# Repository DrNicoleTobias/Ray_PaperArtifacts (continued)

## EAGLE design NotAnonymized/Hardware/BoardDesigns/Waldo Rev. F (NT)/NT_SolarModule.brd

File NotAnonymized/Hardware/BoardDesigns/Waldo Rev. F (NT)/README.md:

#Waldo Rev. F (NT)
Status:  Currently being developed/tested - Under construction.

This folder contains all of the board and schematic files associated with the three Waldo modules (Solar Processing, MCU, and Radio Modules).  Gerbers generated from these files are zipped by module and also included in the Gerbers folder.  References to modified notes associated with Rev D are located in the References folder for the meantime.  A complete BOM as of this date is included and separated by module along with a combined list for ordering for all three modules at once.   The makefile that is included only provides a clean tag to help clean up any of the junk files from this folder as users edit the .brd and .sch files, if they choose to use it.

Current operating version (This is the version used in the ITW deployment for TOSN submission):  
(WALDO v2) Solar2 > MCU1 < Radio

-->Note:  Documentation of this Waldo hardware revision has been developed by Nicole Tobias, Oct 2018.  Let me know if you have additional questions or concerns.

Major updates from Rev. D PCB:
(- removed, + added, +/- modified)
v0
	+/- MCU has been upgraded to a MSP430FR5994 microcontroller.
	+/- Modified how the modules interconnect and modified shape to be smaller and more linear for ease of developing a case to if needed for this PCB..
	+ Added the ability to be able to capture raw wave forms and added active probe circuitry to accomplish reading these signals without effecting them by reading them.
	+/- Changed many of the exposed headers to be probe pads instead to reduce space when not needed, and to help uncomplicate soldering tasks later.
	+/- Changed all possible resistors and capacitors to 0603, instead of 0805 to help reduce space as well.
	- Removed Real-Time Clock, Digipots, etc circuitry to clean up design since they were not being populated in Rev. D.
	+/- Combined both solar boards into one board.
	+ Switch added to solar board to assist with discharging capacitors when needed.
	+/- Switches on MCU module for external battery power, replaced with a jumper to reduce space and confusion on board.
v1
	+ added a 47k resistor and 2.2nF capacitor on the reset pin as specified on the datasheet
	+ added version number to brd silkscreen
	+/- removed +3V3 parts from schematic and changed to DVCC labels for readability and to lower confusion.
v2
	+/- changed resistor and capacitor values on the filters and resistor dividers to decrease power loss over those parts of the circuit.
	+ added connections on the solar board to allow for raw signal reading by the MCU module.
	+/- Moved low pass filters out of the path of the harvesting circuit on the solar board.

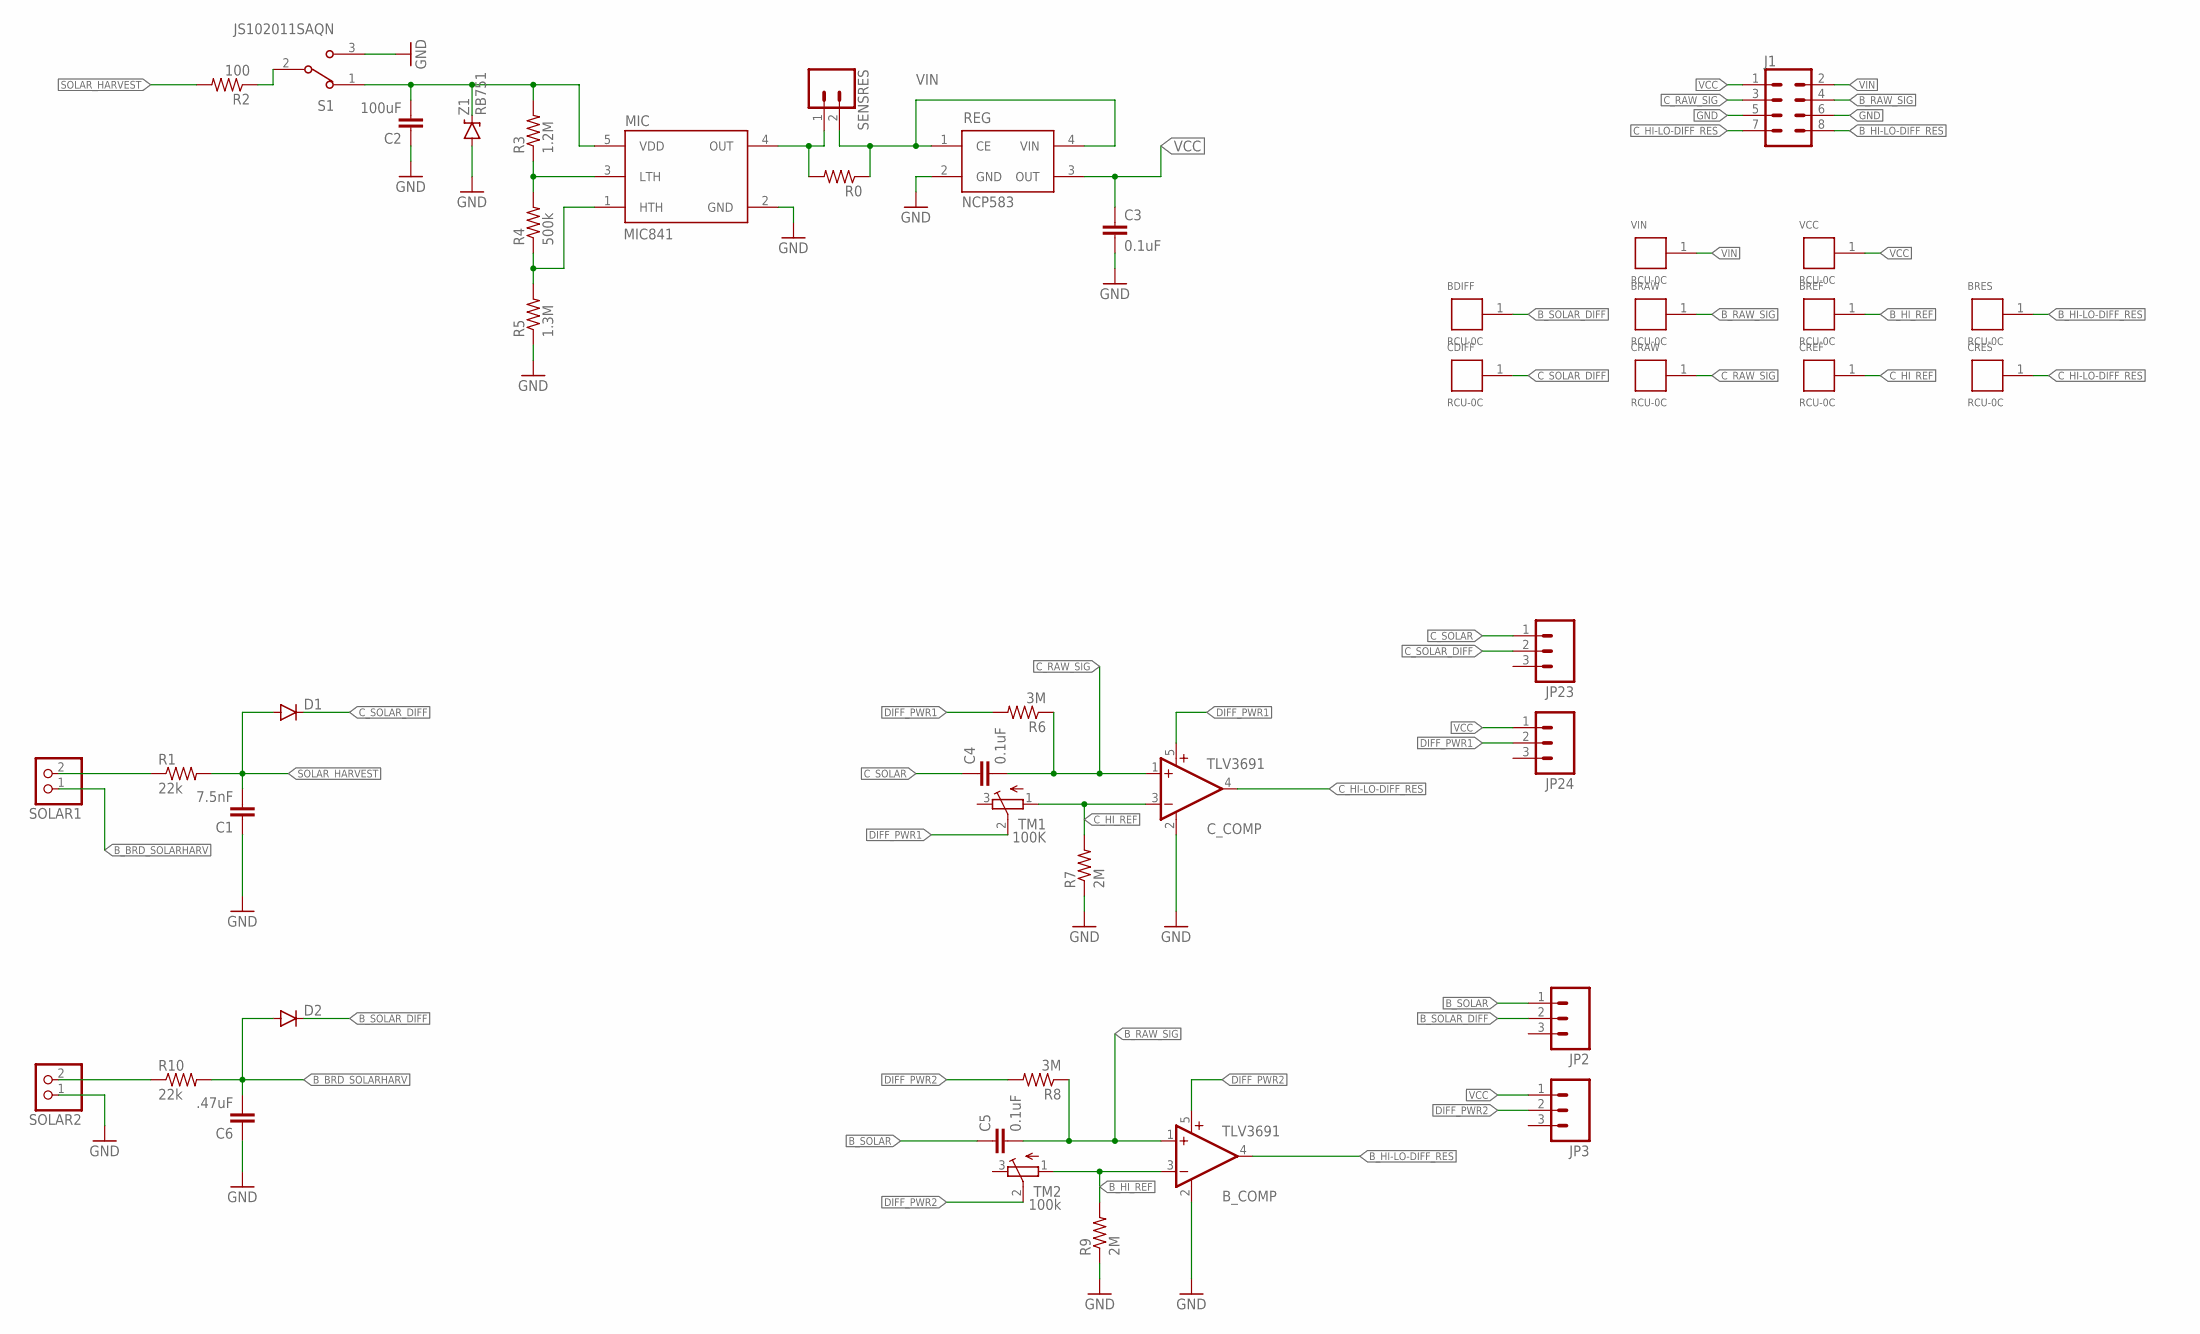
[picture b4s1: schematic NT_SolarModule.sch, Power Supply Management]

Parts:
BDIFF: RCU-0C; TE_RCU-0C
BRAW: RCU-0C; TE_RCU-0C
BREF: RCU-0C; TE_RCU-0C
BRES: RCU-0C; TE_RCU-0C
B_COMP: TLV3691; SC70-5
C1: 7.5nF; 0603-CAP
C2: 100uF; 0603-CAP
C3, C4, C5: 0.1uF; 0603-CAP
C6: .47uF; 0603-CAP
CDIFF: RCU-0C; TE_RCU-0C
CRAW: RCU-0C; TE_RCU-0C
CREF: RCU-0C; TE_RCU-0C
CRES: RCU-0C; TE_RCU-0C
C_COMP: TLV3691; SC70-5
D1, D2: DIODESOD523; SOD523
J1: CONN_04X2; 2X4
JP2, JP3, JP23, JP24: M03; 1X03-1.27MM
MIC: MIC841; SC70-5
R0: RESISTOR0603; 0603-RES
R1, R10: 22k; 0603-RES
R2: 100; 0603-RES
R3: 1.2M; 0603-RES
R4: 500k; 0603-RES
R5: 1.3M; 0603-RES
R6, R8: 3M; 0603-RES
R7, R9: 2M; 0603-RES
REG: NCP583; SC82-AB_1PRIMARY
S1: JS102011SAQN; SW_JS102011SAQN
SENSRES: CONN_02; 1X02
SOLAR1, SOLAR2: PINHD-1X2; 1X02
TM1: 100K; TC33X
TM2: 100k; TC33X
VCC: RCU-0C; TE_RCU-0C
VIN: RCU-0C; TE_RCU-0C
Z1: RB751; SOD-523

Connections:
B_BRD_SOLARHARV: C6.2, D2.A, R10.2, SOLAR1.1
B_HI-LO-DIFF_RES: BRES.1, B_COMP.4 (OUT), J1.8
B_HI_REF: BREF.1, B_COMP.3 (-IN), R9.2, TM2.1 (A)
B_RAW_SIG: BRAW.1, B_COMP.1 (+IN), C5.2, J1.4, R8.1
B_SOLAR: C5.1, JP2.1
B_SOLAR_DIFF: BDIFF.1, D2.C, JP2.2
C_HI-LO-DIFF_RES: CRES.1, C_COMP.4 (OUT), J1.7
C_HI_REF: CREF.1, C_COMP.3 (-IN), R7.2, TM1.1 (A)
C_RAW_SIG: C4.2, CRAW.1, C_COMP.1 (+IN), J1.3, R6.1
C_SOLAR: C4.1, JP23.1
C_SOLAR_DIFF: CDIFF.1, D1.C, JP23.2
DIFF_PWR1: C_COMP.5 (V+), JP24.2, R6.2, TM1.2 (S)
DIFF_PWR2: B_COMP.5 (V+), JP3.2, R8.2, TM2.2 (S)
GND: B_COMP.2 (GND), C1.1, C2.1, C3.2, C6.1, C_COMP.2 (GND), J1.5, J1.6, MIC.2 (GND), R5.1, R7.1, R9.1, REG.2 (GND), S1.3, SOLAR2.1, Z1.ANODE (A)
MIC_INPUT: C2.2, MIC.5 (VDD), R3.2, S1.1, Z1.CATHODE (C)
unnamed: MIC.4 (OUT), R0.2, SENSRES.1
unnamed: R2.1, S1.2
unnamed: MIC.3 (LTH), R3.1, R4.2
unnamed: MIC.1 (HTH), R4.1, R5.2
SOLAR1: R1.1, SOLAR1.2
SOLAR2: R10.1, SOLAR2.2
SOLAR_HARVEST: C1.2, D1.A, R1.2, R2.2
VCC: C3.1, J1.1, JP3.1, JP24.1, REG.3 (OUT), VCC.1
VIN: J1.2, R0.1, REG.1 (CE), REG.4 (VIN), SENSRES.2, VIN.1

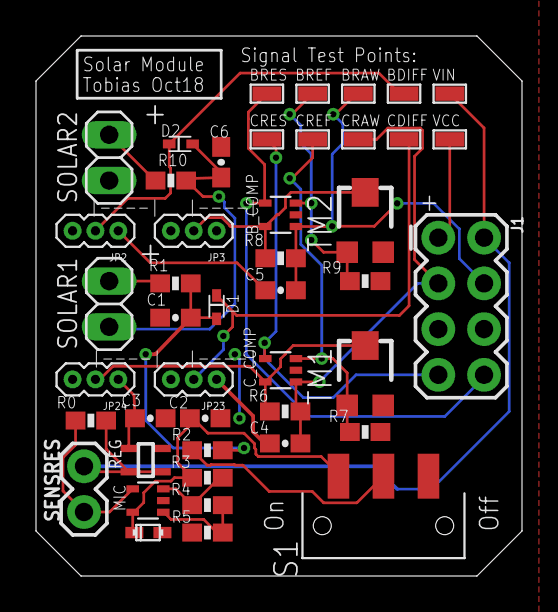
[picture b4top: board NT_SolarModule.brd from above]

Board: 2 copper layers, 27.0 x 30.0 mm, 45 parts (0 on the bottom side), 24 nets.

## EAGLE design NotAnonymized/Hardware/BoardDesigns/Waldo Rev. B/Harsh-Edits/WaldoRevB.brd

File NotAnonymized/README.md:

# RAY

**RAY** is a project whose goal is to accomplish batteryless occupancy detection.  

This repo stores code, hardware files, and other technical documents for the project. Subdirectories are described below.

### Software
Source code, testing code, and documentation.

### Hardware
Hardware PCB version files, 3D enclosures, and documentation.

### Papers
All files, data, and figures used in submission attempts for this project.

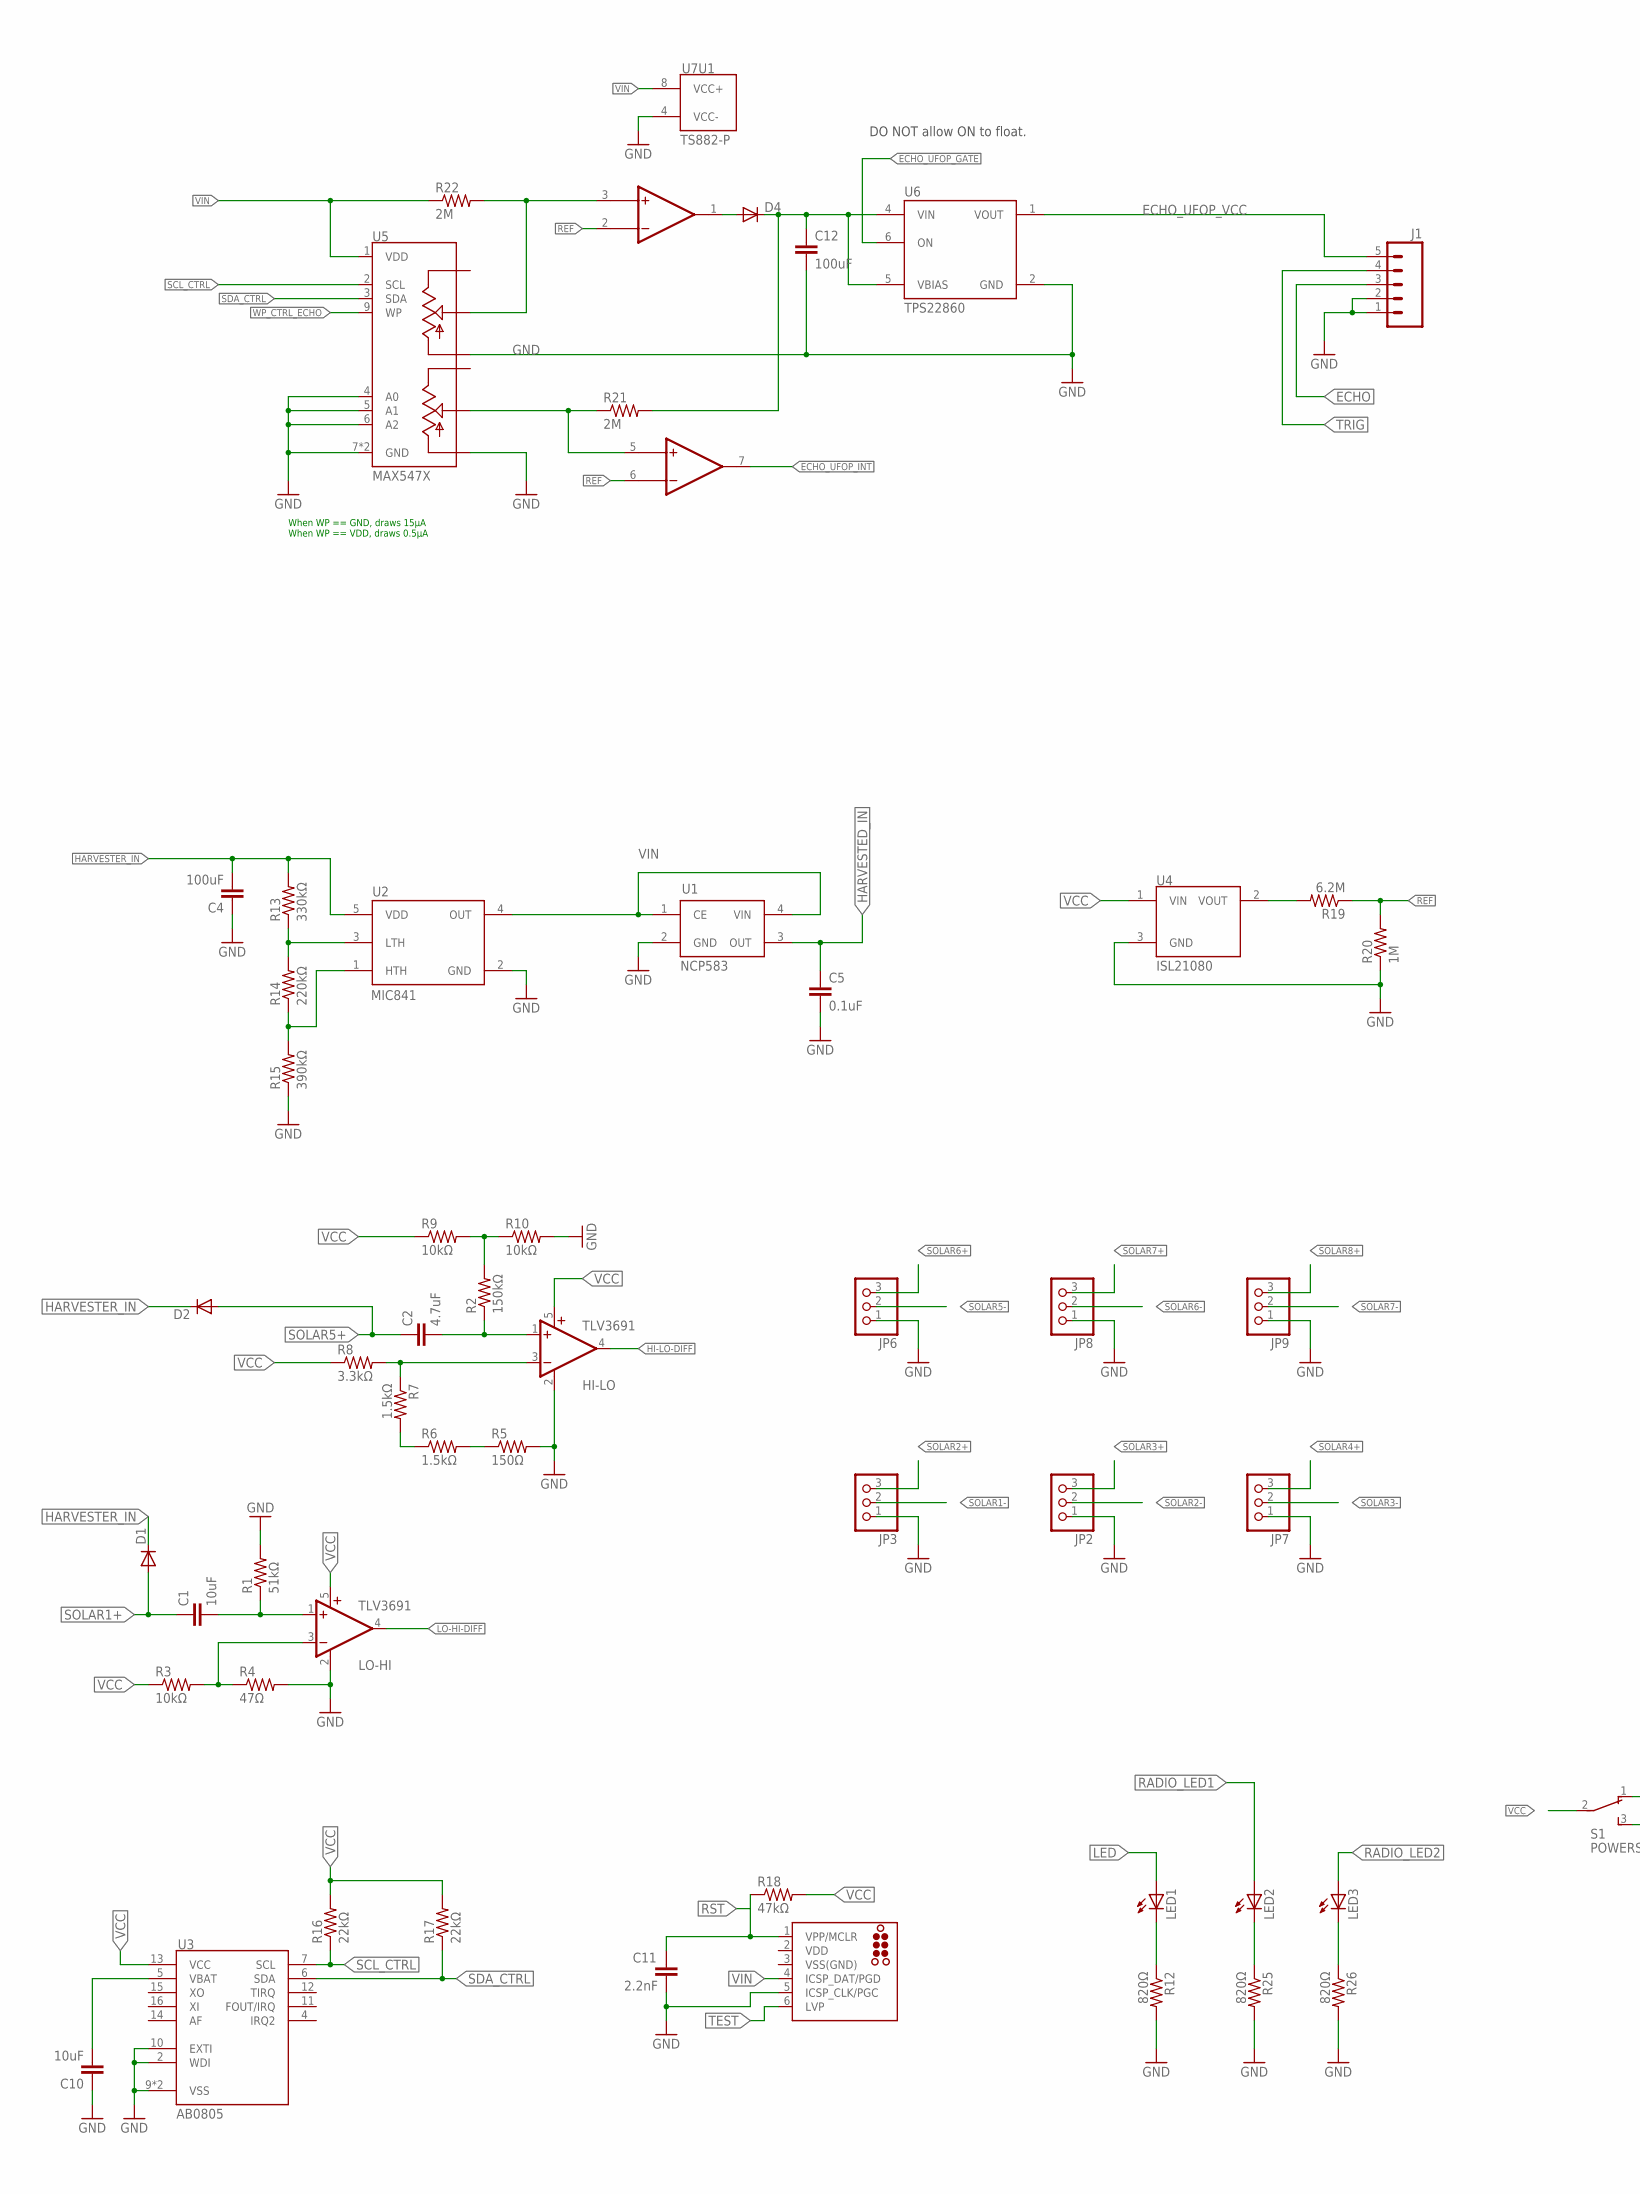
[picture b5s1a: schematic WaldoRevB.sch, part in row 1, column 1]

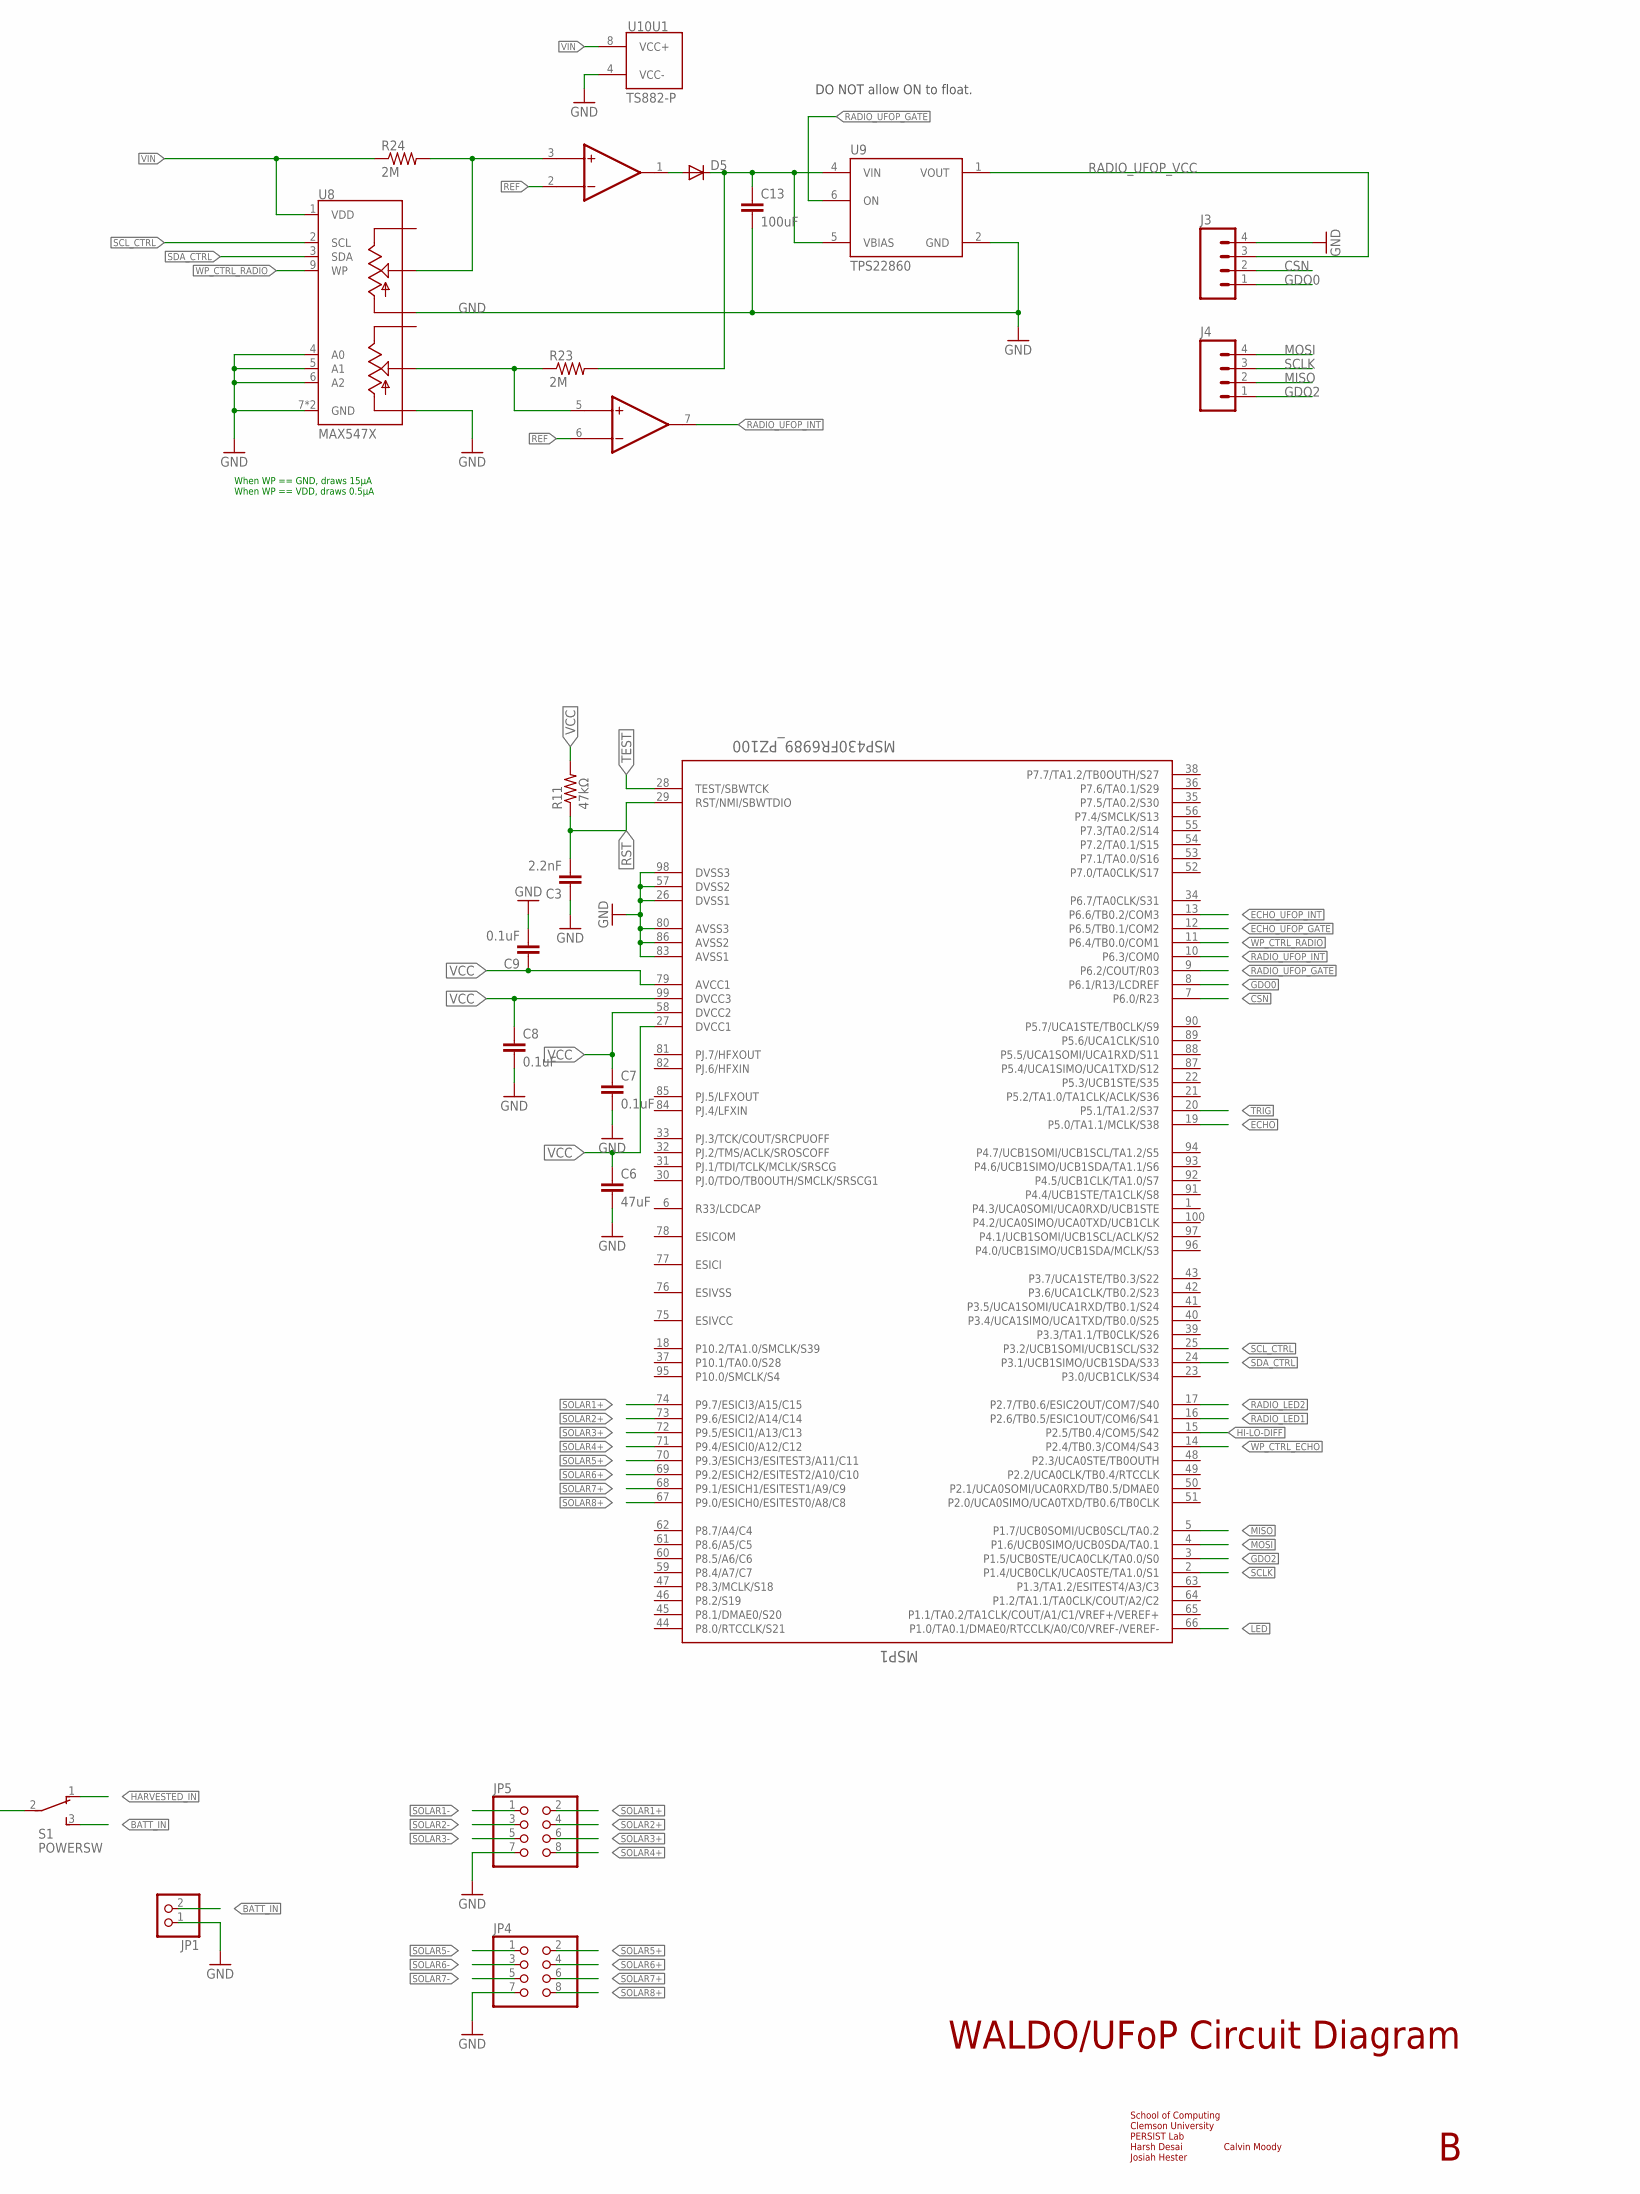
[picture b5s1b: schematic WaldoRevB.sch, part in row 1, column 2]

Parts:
C1, C10: 10uF; 0805
C2: 4.7uF; 0805
C3, C11: 2.2nF; 0805
C4: 100uF; 0805
C5, C7, C8, C9: 0.1uF; 0805
C6: 47uF; 0805
C12, C13: 100uF; 1210; DIGIKEY 490-9969-1-ND
D1, D2: DIODESOD523; SOD523
D4, D5: DIODESOD; SOD-323
HI-LO: TLV3691; SC70-5
J1: M05PTH; 1X05
J2: TC2030-MCP-NL
J3, J4: M04PTH; 1X04
JP1: PINHD-1X2; 1X02
JP2, JP3, JP6, JP7, JP8, JP9: PINHD-1X3; 1X03
JP4, JP5: PINHD-2X4; 2X04
LED1, LED2, LED3: LEDCHIP-LED0805; CHIP-LED0805
LO-HI: TLV3691; SC70-5
MSP1: MSP430FR6989_PZ100; PZ100
R1: 51kΩ; M0805
R2: 150kΩ; M0805
R3, R9, R10: 10kΩ; M0805
R4: 47Ω; M0805
R5: 150Ω; M0805
R6, R7: 1.5kΩ; M0805
R8: 3.3kΩ; M0805
R11, R18: 47kΩ; M0805
R12, R25, R26: 820Ω; M0805
R13: 330kΩ; M0805
R14: 220kΩ; M0805
R15: 390kΩ; M0805
R16, R17: 22kΩ; M0805
R19: 6.2M; 0603; DIGIKEY 541-6.20MHCT-ND
R20: 1M; 0603; DIGIKEY 311-1.00MHRCT-ND
R21, R23: 2M; 0603; DIGIKEY 311-2.00MHRCT-ND
R22, R24: 2M; 0603
S1: POWERSW; TL3XYO
U1: NCP583; SC82-AB_1PRIMARY
U2: MIC841; SC70-5
U3: AB0805; QFN16
U4: ISL21080; SOT-23; DIGIKEY ISL21080DIH309Z-TKCT-ND
U5, U8: MAX547X; QFN16; DIGIKEY MAX5479ETE+-ND
U6, U9: TPS22860; TSOT23-6
U7, U10: TS882-P; UDFN8; DIGIKEY 497-14073-1-ND

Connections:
BATT_IN: JP1.2, S1.3 (S)
CSN: J3.2, MSP1.7 (P6.0/R23)
ECHO: J1.3, MSP1.19 (P5.0/TA1.1/MCLK/S38)
ECHO_UFOP_GATE: MSP1.12 (P6.5/TB0.1/COM2), U6.6 (ON)
ECHO_UFOP_INT: MSP1.13 (P6.6/TB0.2/COM3), U7.7 (OUT1)
ECHO_UFOP_VCC: J1.5, U6.1 (VOUT)
GDO0: J3.1, MSP1.8 (P6.1/R13/LCDREF)
GDO2: J4.1, MSP1.3 (P1.5/UCB0STE/UCA0CLK/TA0.0/S0)
GND: C3.1, C4.1, C5.2, C6.2, C7.2, C8.2, C9.2, C10.1, C11.2, C12.2, C13.2, HI-LO.2 (GND), J1.1, J1.2, J2.5 (ICSP_CLK/PGC), J3.4, JP1.1, JP2.1, JP3.1, JP4.7, JP5.7, JP6.1, JP7.1, JP8.1, JP9.1, LO-HI.2 (GND), MSP1.26 (DVSS1), MSP1.57 (DVSS2), MSP1.80 (AVSS3), MSP1.83 (AVSS1), MSP1.86 (AVSS2), MSP1.98 (DVSS3), R1.2, R4.2, R5.2, R10.2, R12.2, R15.1, R20.1, R25.2, R26.2, U1.2 (GND), U2.2 (GND), U3.2 (WDI), U3.9 (VSS), U3.10 (EXTI), U3.TH (VSS), U4.3 (GND), U5.4 (A0), U5.5 (A1), U5.6 (A2), U5.7 (GND), U5.10 (LB), U5.13 (LA), U5.TH (GND), U6.2 (GND), U7.4 (VCC-), U8.4 (A0), U8.5 (A1), U8.6 (A2), U8.7 (GND), U8.10 (LB), U8.13 (LA), U8.TH (GND), U9.2 (GND), U10.4 (VCC-)
HARVESTED_IN: C5.1, S1.1 (O), U1.3 (OUT)
HARVESTER_IN: C4.2, D1.C, D2.C, R13.2, U2.5 (VDD)
HI-LO-DIFF: HI-LO.4 (OUT), MSP1.15 (P2.5/TB0.4/COM5/S42)
LED: LED1.A, MSP1.66 (P1.0/TA0.1/DMAE0/RTCCLK/A0/C0/VREF-/VER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)
LO-HI-DIFF: LO-HI.4 (OUT)
MISO: J4.2, MSP1.5 (P1.7/UCB0SOMI/UCB0SCL/TA0.2)
MOSI: J4.4, MSP1.4 (P1.6/UCB0SIMO/UCB0SDA/TA0.1)
unnamed: C1.2, LO-HI.1 (+IN), R1.1
unnamed: C2.2, HI-LO.1 (+IN), R2.1
unnamed: LO-HI.3 (-IN), R3.2, R4.1
unnamed: R5.1, R6.2
unnamed: R6.1, R7.2
unnamed: HI-LO.3 (-IN), R7.1, R8.2
unnamed: LED1.C, R12.1
unnamed: R2.2, R9.2, R10.1
unnamed: LED2.C, R25.1
unnamed: LED3.C, R26.1
unnamed: R13.1, R14.2, U2.3 (LTH)
unnamed: R14.1, R15.2, U2.1 (HTH)
unnamed: C10.2, U3.5 (VBAT)
unnamed: R19.2, U4.2 (VOUT)
unnamed: R22.2, U5.14 (WA), U7.3 (IN1+)
unnamed: C12.1, D4.1 (C), R21.2, U6.4 (VIN), U6.5 (VBIAS)
unnamed: R21.1, U5.11 (WB), U7.5 (IN1+)
unnamed: D4.2 (A), U7.1 (OUT1)
unnamed: R24.2, U8.14 (WA), U10.3 (IN1+)
unnamed: C13.1, D5.1 (C), R23.2, U9.4 (VIN), U9.5 (VBIAS)
unnamed: R23.1, U8.11 (WB), U10.5 (IN1+)
unnamed: D5.2 (A), U10.1 (OUT1)
RADIO_LED1: LED2.A, MSP1.16 (P2.6/TB0.5/ESIC1OUT/COM6/S41)
RADIO_LED2: LED3.A, MSP1.17 (P2.7/TB0.6/ESIC2OUT/COM7/S40)
RADIO_UFOP_GATE: MSP1.9 (P6.2/COUT/R03), U9.6 (ON)
RADIO_UFOP_INT: MSP1.10 (P6.3/COM0), U10.7 (OUT1)
RADIO_UFOP_VCC: J3.3, U9.1 (VOUT)
REF: R19.1, R20.2, U7.2 (IN1-), U7.6 (IN1-), U10.2 (IN1-), U10.6 (IN1-)
RST: C3.2, C11.1, J2.1 (VPP/MCLR), MSP1.29 (RST/NMI/SBWTDIO), R11.1, R18.1
SCLK: J4.3, MSP1.2 (P1.4/UCB0CLK/UCA0STE/TA1.0/S1)
SCL_CTRL: MSP1.25 (P3.2/UCB1SOMI/UCB1SCL/S32), R16.1, U3.7 (SCL), U5.2 (SCL), U8.2 (SCL)
SDA_CTRL: MSP1.24 (P3.1/UCB1SIMO/UCB1SDA/S33), R17.1, U3.6 (SDA), U5.3 (SDA), U8.3 (SDA)
SOLAR1+: C1.1, D1.A, JP5.2, MSP1.74 (P9.7/ESICI3/A15/C15)
SOLAR1-: JP3.2, JP5.1
SOLAR2+: JP3.3, JP5.4, MSP1.73 (P9.6/ESICI2/A14/C14)
SOLAR2-: JP2.2, JP5.3
SOLAR3+: JP2.3, JP5.6, MSP1.72 (P9.5/ESICI1/A13/C13)
SOLAR3-: JP5.5, JP7.2
SOLAR4+: JP5.8, JP7.3, MSP1.71 (P9.4/ESICI0/A12/C12)
SOLAR5+: C2.1, D2.A, JP4.2, MSP1.70 (P9.3/ESICH3/ESITEST3/A11/C11)
SOLAR5-: JP4.1, JP6.2
SOLAR6+: JP4.4, JP6.3, MSP1.69 (P9.2/ESICH2/ESITEST2/A10/C10)
SOLAR6-: JP4.3, JP8.2
SOLAR7+: JP4.6, JP8.3, MSP1.68 (P9.1/ESICH1/ESITEST1/A9/C9)
SOLAR7-: JP4.5, JP9.2
SOLAR8+: JP4.8, JP9.3, MSP1.67 (P9.0/ESICH0/ESITEST0/A8/C8)
TEST: J2.6 (LVP), MSP1.28 (TEST/SBWTCK)
TRIG: J1.4, MSP1.20 (P5.1/TA1.2/S37)
VCC: C6.1, C7.1, C8.1, C9.1, HI-LO.5 (V+), LO-HI.5 (V+), MSP1.27 (DVCC1), MSP1.58 (DVCC2), MSP1.79 (AVCC1), MSP1.99 (DVCC3), R3.1, R8.1, R9.1, R11.2, R16.2, R17.2, R18.2, S1.2, U3.13 (VCC), U4.1 (VIN)
VDD: J2.2 (VDD)
VIN: J2.4 (ICSP_DAT/PGD), R22.1, R24.1, U1.1 (CE), U1.4 (VIN), U2.4 (OUT), U5.1 (VDD), U7.8 (VCC+), U8.1 (VDD), U10.8 (VCC+)
VSS(GND): J2.3 (VSS(GND))
WP_CTRL_ECHO: MSP1.14 (P2.4/TB0.3/COM4/S43), U5.9 (WP)
WP_CTRL_RADIO: MSP1.11 (P6.4/TB0.0/COM1), U8.9 (WP)

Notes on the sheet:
DO NOT allow ON to float.
When WP == GND, draws 15µA When WP == VDD, draws 0.5µA
WALDO/UFoP Circuit Diagram
School of Computing Clemson University PERSIST Lab Harsh Desai Calvin Moody Josiah Hester

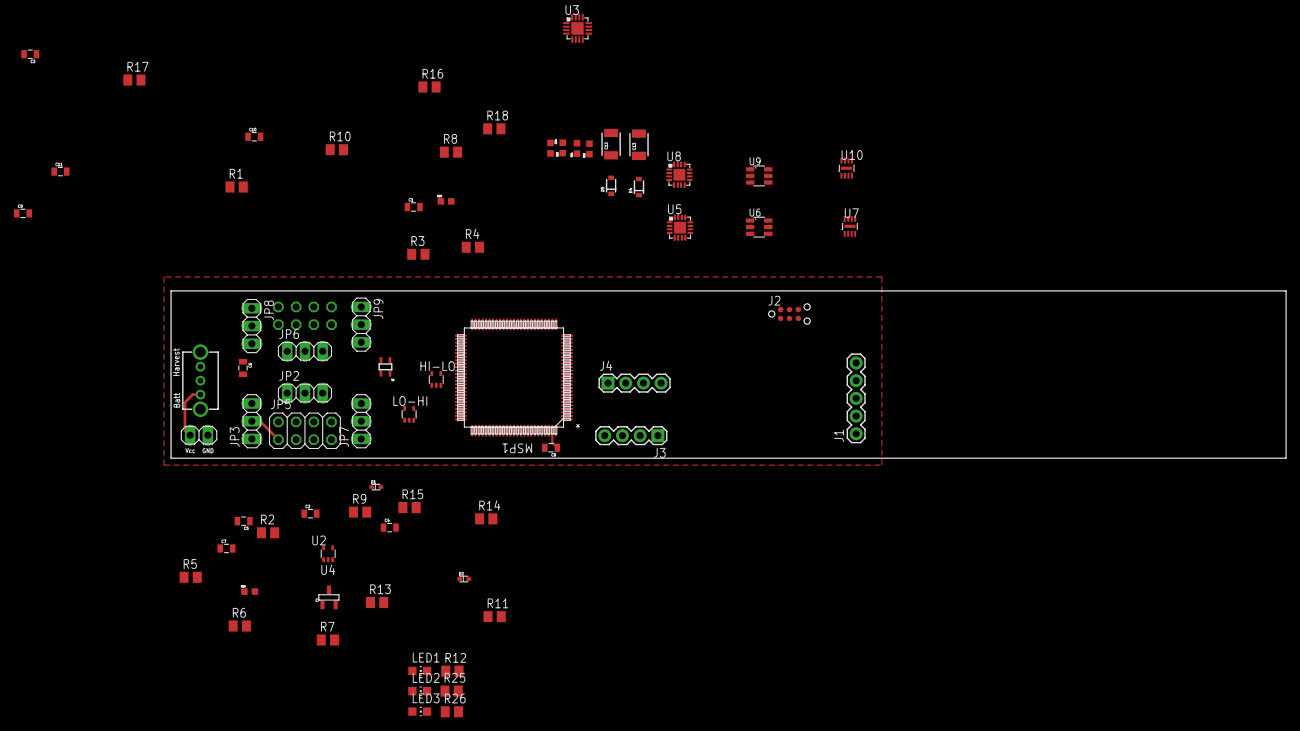
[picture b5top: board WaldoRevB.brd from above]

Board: 2 copper layers, 160.0 x 24.0 mm, 73 parts (1 on the bottom side), 67 nets.

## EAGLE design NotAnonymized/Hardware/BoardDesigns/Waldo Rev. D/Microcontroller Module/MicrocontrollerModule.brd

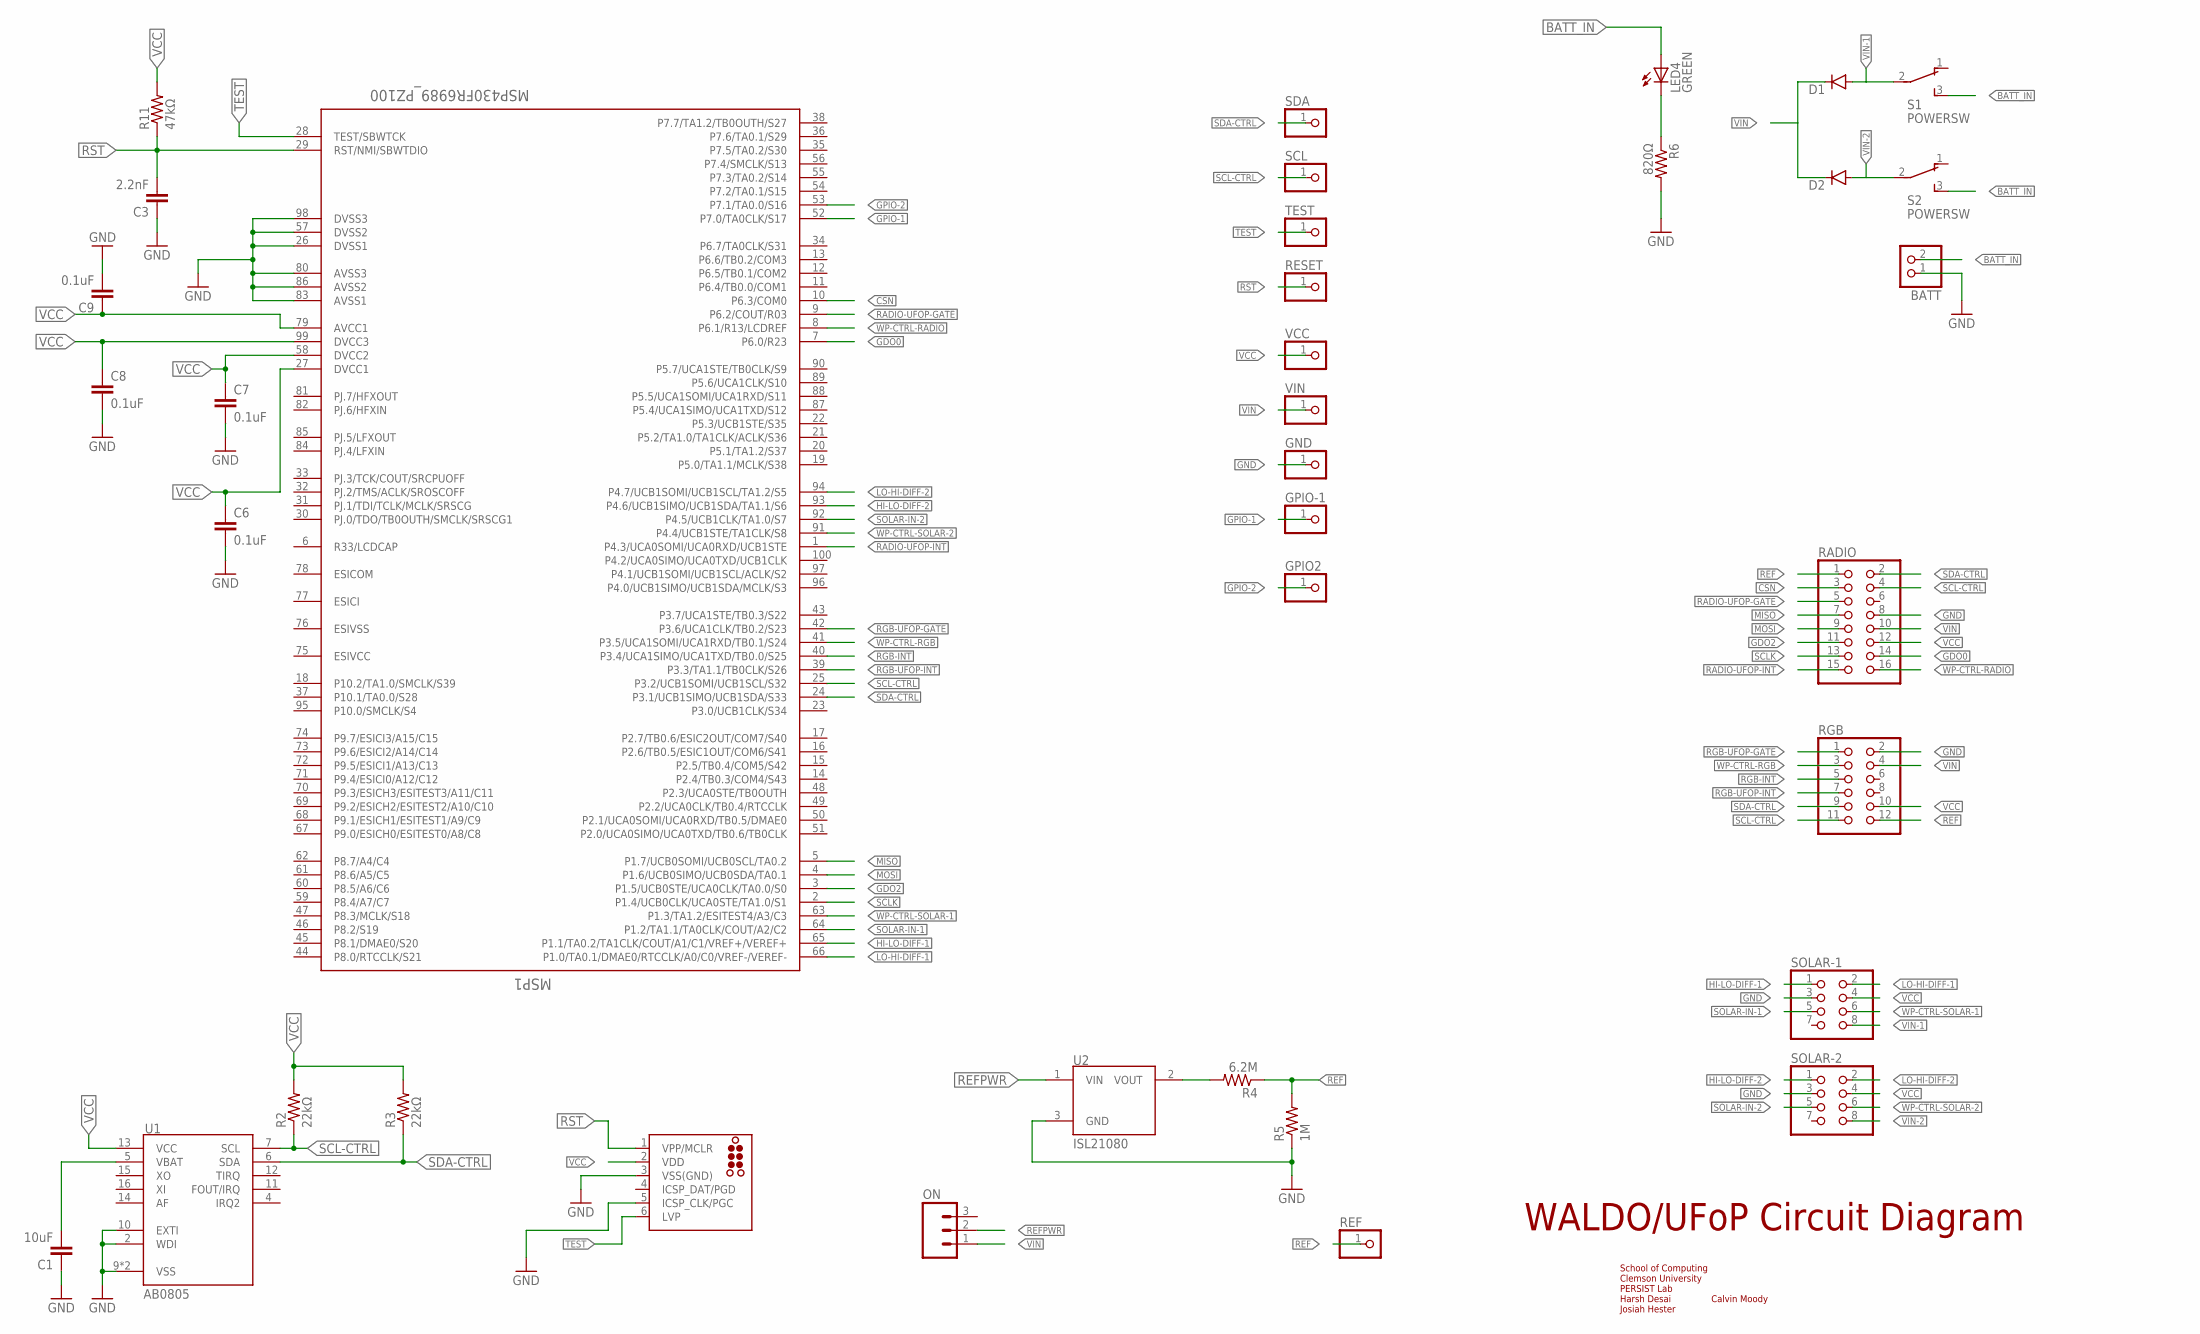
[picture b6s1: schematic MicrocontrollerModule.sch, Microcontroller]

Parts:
BATT: PINHD-1X2; 1X02
C1: 10uF; 0805
C3: 2.2nF; 0805
C6, C7, C8, C9: 0.1uF; 0805
D1, D2: DIODESOD523; SOD523
GND: PINHD-1X1; 1X01
GPIO2: PINHD-1X1; 1X01
GPIO-1: PINHD-1X1; 1X01
J1: TC2030-MCP-NL
LED4: GREEN; CHIP-LED0805
MSP1: MSP430FR6989_PZ100; PZ100
ON: M03; 1X03-1.27MM
R2, R3: 22kΩ; 0805
R4: 6.2M; 0805; DIGIKEY 541-6.20MHCT-ND
R5: 1M; 0805; DIGIKEY 311-1.00MHRCT-ND
R6: 820Ω; 0805
R11: 47kΩ; 0805
RADIO: PINHD-2X8/90; 2X08/90
REF: PINHD-1X1; 1X01
RESET: PINHD-1X1; 1X01
RGB: PINHD-2X6/90; 2X06/90
S1, S2: POWERSW; TL3XYO
SCL: PINHD-1X1; 1X01
SDA: PINHD-1X1; 1X01
SOLAR-1, SOLAR-2: PINHD-2X4/90; 2X04/90
TEST: PINHD-1X1; 1X01
U1: AB0805; QFN16
U2: ISL21080; SOT-23; DIGIKEY ISL21080DIH309Z-TKCT-ND
VCC: PINHD-1X1; 1X01
VIN: PINHD-1X1; 1X01

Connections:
BATT_IN: BATT.2, LED4.A, S1.3 (S), S2.3 (S)
CSN: MSP1.10 (P6.3/COM0), RADIO.3
GDO0: MSP1.7 (P6.0/R23), RADIO.14
GDO2: MSP1.3 (P1.5/UCB0STE/UCA0CLK/TA0.0/S0), RADIO.11
GND: BATT.1, C1.1, C3.1, C6.2, C7.2, C8.2, C9.2, GND.1, J1.3 (VSS(GND)), J1.5 (ICSP_CLK/PGC), MSP1.26 (DVSS1), MSP1.57 (DVSS2), MSP1.80 (AVSS3), MSP1.83 (AVSS1), MSP1.86 (AVSS2), MSP1.98 (DVSS3), R5.1, R6.2, RADIO.8, RGB.2, SOLAR-1.3, SOLAR-2.3, U1.2 (WDI), U1.9 (VSS), U1.10 (EXTI), U1.TH (VSS), U2.3 (GND)
GPIO-1: GPIO-1.1, MSP1.52 (P7.0/TA0CLK/S17)
GPIO-2: GPIO2.1, MSP1.53 (P7.1/TA0.0/S16)
HI-LO-DIFF-1: MSP1.65 (P1.1/TA0.2/TA1CLK/COUT/A1/C1/VREF+/VERE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), SOLAR-1.1
HI-LO-DIFF-2: MSP1.93 (P4.6/UCB1SIMO/UCB1SDA/TA1.1/S6), SOLAR-2.1
LO-HI-DIFF-1: MSP1.66 (P1.0/TA0.1/DMAE0/RTCCLK/A0/C0/VREF-/VER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), SOLAR-1.2
LO-HI-DIFF-2: MSP1.94 (P4.7/UCB1SOMI/UCB1SCL/TA1.2/S5), SOLAR-2.2
MISO: MSP1.5 (P1.7/UCB0SOMI/UCB0SCL/TA0.2), RADIO.7
MOSI: MSP1.4 (P1.6/UCB0SIMO/UCB0SDA/TA0.1), RADIO.9
unnamed: C1.2, U1.5 (VBAT)
unnamed: LED4.C, R6.1
unnamed: R4.2, U2.2 (VOUT)
RADIO-UFOP-GATE: MSP1.9 (P6.2/COUT/R03), RADIO.5
RADIO-UFOP-INT: MSP1.1 (P4.3/UCA0SOMI/UCA0RXD/UCB1STE), RADIO.15
REF: R4.1, R5.2, RADIO.1, REF.1, RGB.12
REFPWR: ON.2, U2.1 (VIN)
RGB-INT: MSP1.40 (P3.4/UCA1SIMO/UCA1TXD/TB0.0/S25), RGB.5
RGB-UFOP-GATE: MSP1.42 (P3.6/UCA1CLK/TB0.2/S23), RGB.1
RGB-UFOP-INT: MSP1.39 (P3.3/TA1.1/TB0CLK/S26), RGB.7
RST: C3.2, J1.1 (VPP/MCLR), MSP1.29 (RST/NMI/SBWTDIO), R11.1, RESET.1
SCL-CTRL: MSP1.25 (P3.2/UCB1SOMI/UCB1SCL/S32), R2.1, RADIO.4, RGB.11, SCL.1, U1.7 (SCL)
SCLK: MSP1.2 (P1.4/UCB0CLK/UCA0STE/TA1.0/S1), RADIO.13
SDA-CTRL: MSP1.24 (P3.1/UCB1SIMO/UCB1SDA/S33), R3.1, RADIO.2, RGB.9, SDA.1, U1.6 (SDA)
SOLAR-IN-1: MSP1.64 (P1.2/TA1.1/TA0CLK/COUT/A2/C2), SOLAR-1.5
SOLAR-IN-2: MSP1.92 (P4.5/UCB1CLK/TA1.0/S7), SOLAR-2.5
TEST: J1.6 (LVP), MSP1.28 (TEST/SBWTCK), TEST.1
VCC: C6.1, C7.1, C8.1, C9.1, J1.2 (VDD), MSP1.27 (DVCC1), MSP1.58 (DVCC2), MSP1.79 (AVCC1), MSP1.99 (DVCC3), R2.2, R3.2, R11.2, RADIO.12, RGB.10, SOLAR-1.4, SOLAR-2.4, U1.13 (VCC), VCC.1
VIN: D1.C, D2.C, ON.1, RADIO.10, RGB.4, VIN.1
VIN-1: D1.A, S1.2, SOLAR-1.8
VIN-2: D2.A, S2.2, SOLAR-2.8
WP-CTRL-RADIO: MSP1.8 (P6.1/R13/LCDREF), RADIO.16
WP-CTRL-RGB: MSP1.41 (P3.5/UCA1SOMI/UCA1RXD/TB0.1/S24), RGB.3
WP-CTRL-SOLAR-1: MSP1.63 (P1.3/TA1.2/ESITEST4/A3/C3), SOLAR-1.6
WP-CTRL-SOLAR-2: MSP1.91 (P4.4/UCB1STE/TA1CLK/S8), SOLAR-2.6

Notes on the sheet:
WALDO/UFoP Circuit Diagram
School of Computing Clemson University PERSIST Lab Harsh Desai Calvin Moody Josiah Hester

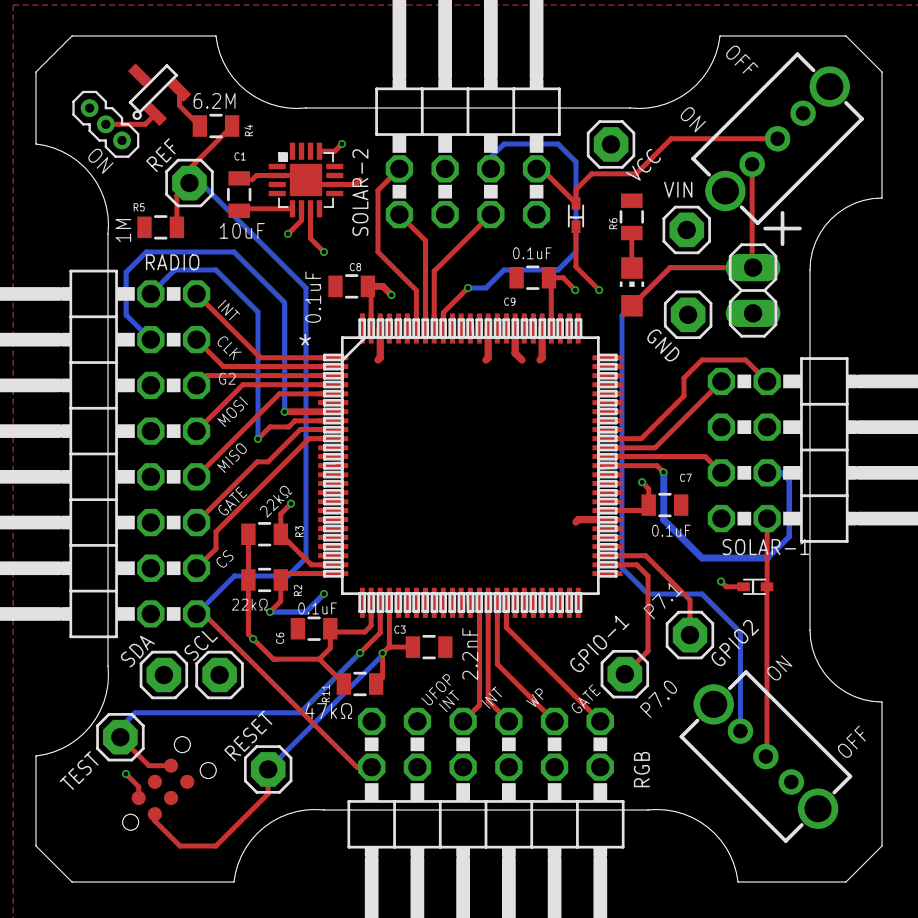
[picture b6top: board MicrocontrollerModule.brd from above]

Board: 4 copper layers, 47.0 x 47.0 mm, 37 parts (0 on the bottom side), 38 nets.
